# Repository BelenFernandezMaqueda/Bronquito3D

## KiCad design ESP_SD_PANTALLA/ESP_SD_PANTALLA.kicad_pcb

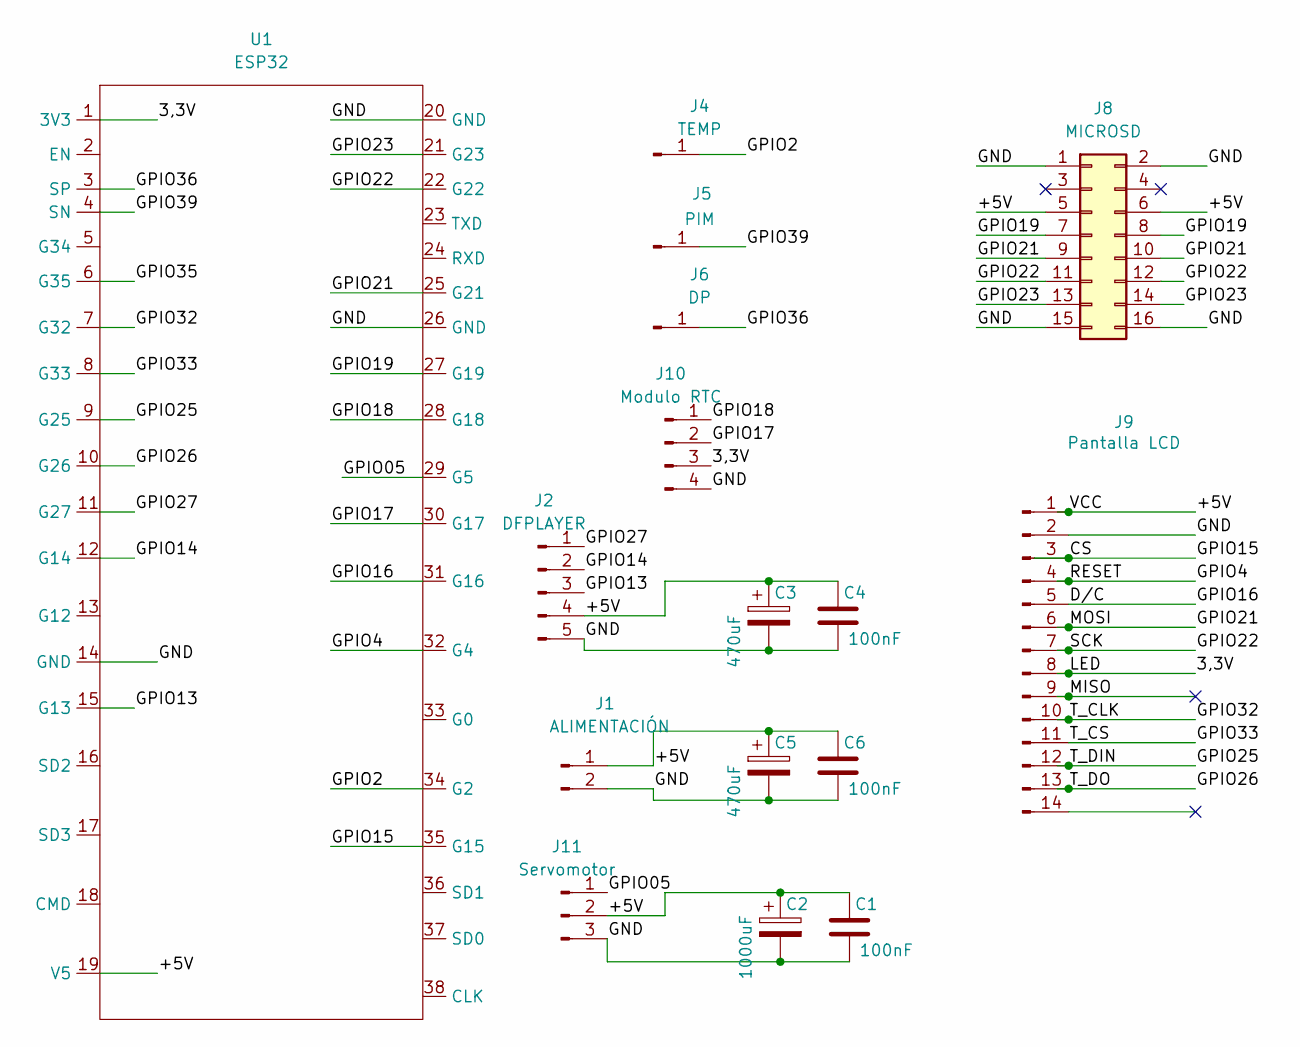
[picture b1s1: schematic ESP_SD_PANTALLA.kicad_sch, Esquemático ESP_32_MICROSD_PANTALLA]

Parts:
C1, C4, C6: 100nF; C_Disc_D5.0mm_W2.5mm_P2.50mm
C2: 1000uF; CP_Radial_D5.0mm_P2.50mm
C3, C5: 470uF; CP_Radial_D5.0mm_P2.50mm
J1: ALIMENTACIÓN; PinSocket_1x02_P2.54mm_Vertical
J2: DFPLAYER; PinSocket_1x05_P2.54mm_Vertical
J4: TEMP; PinSocket_1x01_P2.54mm_Vertical
J5: PIM; PinSocket_1x01_P2.54mm_Vertical
J6: DP; PinSocket_1x01_P2.54mm_Vertical
J8: MICROSD; PinSocket_2x08_P2.54mm_Vertical
J9: Pantalla LCD; PinSocket_1x14_P2.54mm_Vertical
J10: Modulo RTC; PinSocket_1x04_P2.54mm_Vertical
J11: Servomotor; PinSocket_1x03_P2.54mm_Vertical
U1: ESP32

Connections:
/3,3V: J9.8, J10.3, U1.1 (3V3)
/+5V: C1.1, C2.1, C3.1, C4.1, C5.1, C6.1, J1.1, J2.4, J8.5, J8.6, J9.1, J11.2, U1.19 (V5)
/CS: J9.3, U1.35 (G15)
/D/C: J9.5, U1.31 (G16)
/GND: C1.2, C2.2, C3.2, C4.2, C5.2, C6.2, J1.2, J2.5, J8.1, J8.2, J8.15, J8.16, J9.2, J10.4, J11.3, U1.14 (GND), U1.20 (GND), U1.26 (GND)
/GPIO2: J4.1 (Pin_1_1), U1.34 (G2)
/GPIO4: J9.4, U1.32 (G4)
/GPIO05: J11.1, U1.29 (G5)
/GPIO13: J2.3, U1.15 (G13)
/GPIO14: J2.2, U1.12 (G14)
/GPIO17: J10.2, U1.30 (G17)
/GPIO18: J10.1, U1.28 (G18)
/GPIO19: J8.7, J8.8, U1.27 (G19)
/GPIO21: J8.9, J8.10, J9.6, U1.25 (G21)
/GPIO22: J8.11, J8.12, J9.7, U1.22 (G22)
/GPIO23: J8.13, J8.14, U1.21 (G23)
/GPIO25: J9.12, U1.9 (G25)
/GPIO26: J9.13, U1.10 (G26)
/GPIO27: J2.1, U1.11 (G27)
/GPIO32: J9.10, U1.7 (G32)
/GPIO33: J9.11, U1.8 (G33)
/GPIO35: U1.6 (G35)
/GPIO36: J6.1 (Pin_1_1), U1.3 (SP)
/GPIO39: J5.1 (Pin_1_1), U1.4 (SN)
/MISO: J9.9

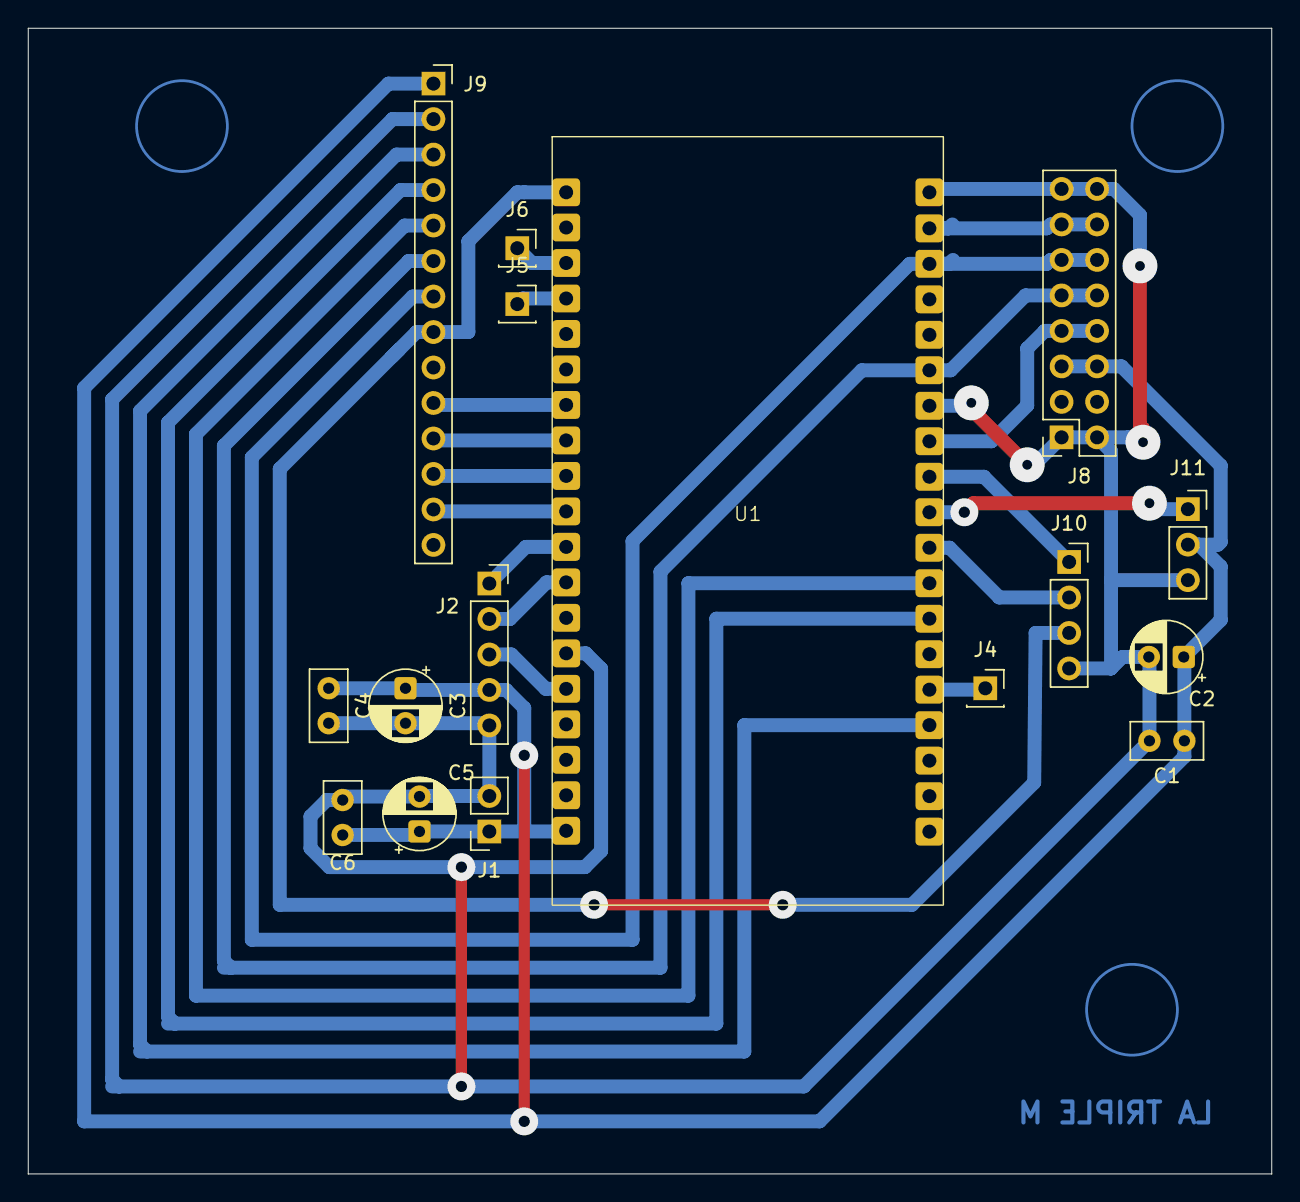
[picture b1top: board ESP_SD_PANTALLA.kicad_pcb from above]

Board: 2 copper layers, 89.0 x 82.0 mm, 16 parts (0 on the bottom side), 23 nets.

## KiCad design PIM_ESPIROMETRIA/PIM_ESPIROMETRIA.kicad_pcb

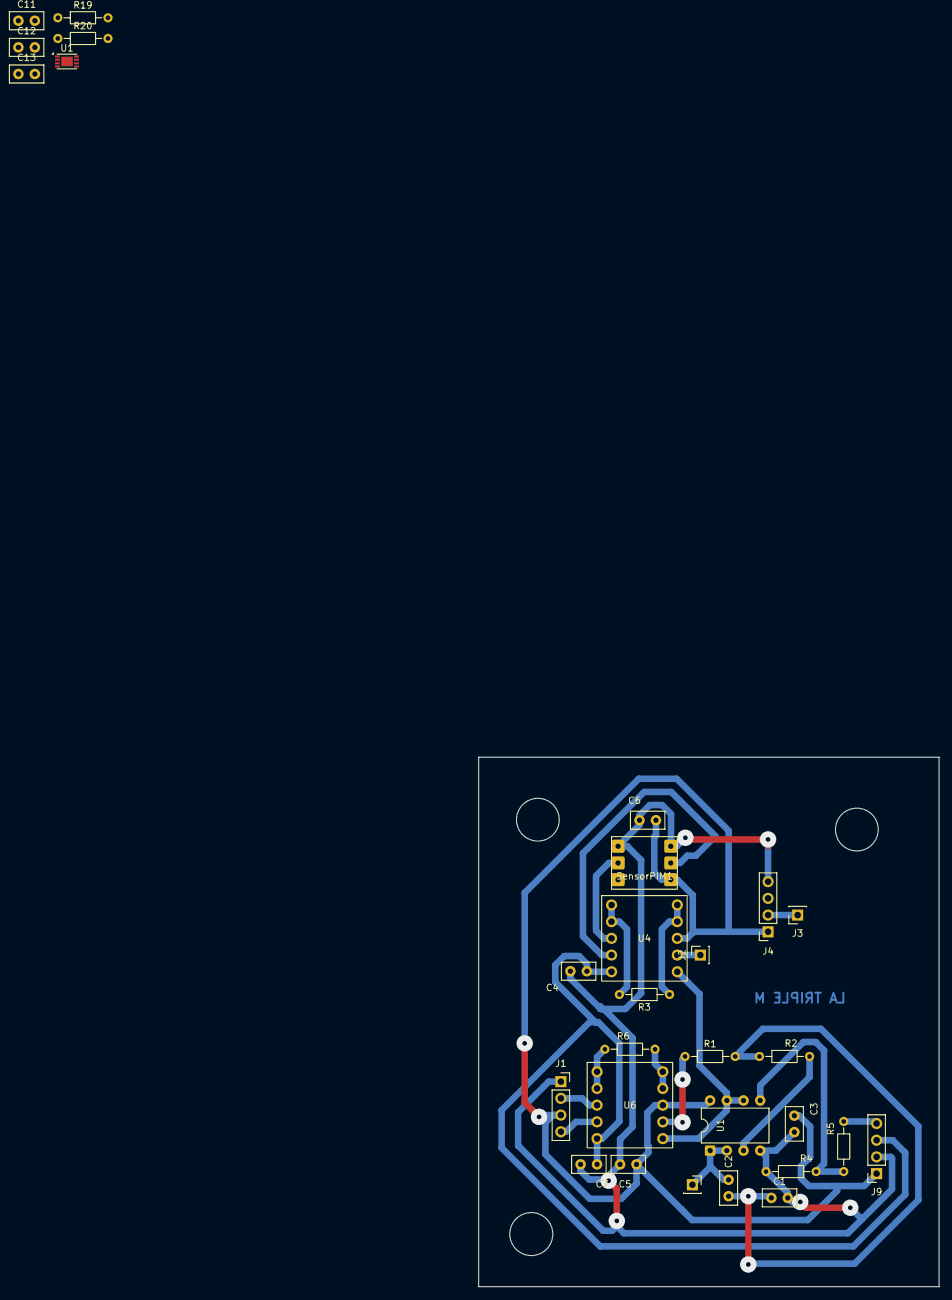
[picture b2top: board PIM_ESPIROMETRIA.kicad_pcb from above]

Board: 2 copper layers, 70.0 x 80.5 mm, 29 parts (0 on the bottom side), 20 nets.

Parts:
C1: 47nF; C_Disc_D5.0mm_W2.5mm_P2.50mm
C2, C3, C4, C5, C6, C7, C11, C12, C13: 100nF; C_Disc_D5.0mm_W2.5mm_P2.50mm
J1: Sensor Diferencial de Presión; PinSocket_1x04_P2.54mm_Vertical
J2: Salida PIM; PinSocket_1x01_P2.54mm_Vertical
J3: Salida TEMP; PinSocket_1x01_P2.54mm_Vertical
J4: TEMP; PinSocket_1x04_P2.54mm_Vertical
J5: Salida DP; PinSocket_1x01_P2.54mm_Vertical
J9: Alimentación; PinSocket_1x04_P2.54mm_Vertical
R1, R2: 47k; R_Axial_DIN0204_L3.6mm_D1.6mm_P7.62mm_Horizontal
R3: 12.4k; R_Axial_DIN0204_L3.6mm_D1.6mm_P7.62mm_Horizontal
R4, R5, R19, R20: 1k; R_Axial_DIN0204_L3.6mm_D1.6mm_P7.62mm_Horizontal
R6: 511; R_Axial_DIN0204_L3.6mm_D1.6mm_P7.62mm_Horizontal
SensorPIM1: Sin título
U1: MCP6004; DFN-8-1EP_3x2mm_P0.5mm_EP1.75x1.45mm
U1#2: LM358; DIP-8_W7.62mm
U4, U6: Sin título

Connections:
/1.65V: U1.1, U1.2 (-), U1#2.6 (-), U1#2.7, U6.5 (Vref)
/2.5V: U1.6 (-), U1.7, U4.5 (Vref)
/3.3V: C12.2, C13.1, J9.4, R5.1, U1.4 (V+)
/+5V: C3.1, C5.2, C6.2, J1.3, J4.1, J9.1, SensorPIM1.3 (VS+), U1#2.8 (V+), U4.3 (VS+), U6.3 (VS+)
/-5V: C4.2, C7.2, J9.3
/DP: C2.1, U1.8, U1.9 (-), U1#2.1, U1#2.2 (-)
/GND: C1.2, C3.2, C4.1, C5.1, C6.1, C7.1, C11.1, C12.1, C13.2, J1.1, J4.4, J9.2, R4.2, R20.2, SensorPIM1.1 (GND), SensorPIM1.6 (GND), U1#2.4 (V-), U4.6 (VS-), U6.6 (VS-)
/GPIO07: J3.1 (Pin_1_1), J4.2
/OUTPUT+: J1.4, U6.7 (IN+)
/OUTPUT-: J1.2, U6.8 (IN-)
/VOUT+: SensorPIM1.2 (V0+), U4.7 (IN+)
/VOUT-: SensorPIM1.5 (VO-), U4.8 (IN-)
unnamed: C1.1, C2.2, R1.2, R2.1
unnamed: R3.1, U4.1 (RG), U4.2 (RG)
unnamed: R3.2, U4.9 (RG), U4.10 (RG)
unnamed: R6.1, U6.1 (RG), U6.2 (RG)
unnamed: R6.2, U6.9 (RG), U6.10 (RG)
unnamed: R4.1, R5.2, U1.3 (+), U1#2.3 (+)
unnamed: R19.2, R20.1, U1.5 (+), U1#2.5 (+)
unnamed: R1.1, U6.4 (OUT)
